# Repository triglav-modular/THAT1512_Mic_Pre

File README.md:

# µAmp
A THAT1512 microphone preamp. This is a very simple board with a THAT1512 based preamp for replacing the one in the Buchla 208 for a much lower noise floor and higher gain. Wire between the preamp jack and T.P.1 on card 10. Lower R6 on card 10 to compensate for the gain increase.

The board is 45 × 24 mm with a single M3 mounting hole. Gain is set by the 1K trimmer (RV1, a Bourns 3362P): about 15 dB at full resistance up to about 59 dB at zero, where the 5.6 Ω R6 sets the top of the range.

## Header pinout

Pin 1 is the square pad.

| Pin | 1 | 2 | 3 | 4 | 5 | 6 | 7 |
|---|---|---|---|---|---|---|---|
| | i+ | i− | g | −v | +v | g | out |

## Revisions

**rev3 (2026)** — same outline, header pinout and mounting hole as rev2, so it is a drop-in replacement.

- Corrected part numbers: U1 is THAT1512P08-U (was 1510), C4/C5 are 100 nF (were 470 pF part numbers), R1/R2 are 1 kΩ (were 6.81 kΩ part numbers), RV1 is 1 kΩ.
- R3 100 Ω in series with the output, to isolate the THAT1512 from the capacitance of the wire to card 10 (it is specified for 300 pF at most).
- R6 5.6 Ω in series with RV1, so maximum gain is set by a resistor rather than by the trimmer's end resistance.
- R4/C7 and R5/C8: 10 Ω and 10 µF on each supply rail.
- No output coupling capacitor is needed: card 10 AC-couples after T.P.1, and C6 holds the output offset to a few mV.

**rev2 (2022)** — the board fitted in the 208, tagged `rev2`. Its raytraced render is `uAmp_3D_render.png`.

## Bill of materials (rev3)

| Ref | Value | Part number | Notes |
|---|---|---|---|
| U1 | THAT1512 | THAT1512P08-U | DIP-8 |
| RV1 | 1 kΩ trimmer | Bourns 3362P-1-102LF | |
| C1, C2 | 470 pF | Murata RDE5C2A471J0M1H03A | C0G, 5 mm pitch |
| C3 | 47 pF | Murata RDE5C2A470J0M1H03A | C0G, 5 mm pitch |
| C4, C5 | 100 nF | Murata RDER71H104K0M1H03A | X7R, 5 mm pitch |
| C6 | 6800 µF 6.3 V | Nichicon UVZ0J682MHD | 12.5 × 25 mm, 5 mm pitch. Polarized is correct here: both gain pins sit at the same DC level. Bipolar 6800 µF only comes as 18 × 35.5 mm, which does not fit |
| C7, C8 | 10 µF 50 V | Panasonic EEU-FR1H100 | 5 mm diameter, 2 mm pitch |
| R1, R2 | 1 kΩ 0.1 % | Vishay CMF551K0000BEEK | |
| R3 | 100 Ω | Vishay MBA02040C1000FC100 | mounted vertically |
| R4, R5 | 10 Ω | Vishay MBA02040C1009FC100 | mounted vertically |
| R6 | 5.6 Ω | Vishay MBB02070C5608FCT00 | mounted vertically |
| J1 | 1×7 pin header | | 2.54 mm |

## Substituting the SSM2019

THAT Corporation put the 1510 and 1512 on end-of-life status on 1 September 2026 ([memo](https://thatcorp.com/wp-content/uploads/2026/09/THAT-EOL-Memo.pdf)). The Analog Devices SSM2019BNZ (DIP-8) has the same pinout and fits U1 with no board change.

Its gain is 1 + 10 kΩ/Rg where the THAT1512's is 0.5 + 5 kΩ/Rg, so with the rev3 values the range moves up about 6 dB, to 21–65 dB. Two value changes bring it back to about 15.5–59 dB:

| Ref | With THAT1512 | With SSM2019 |
|---|---|---|
| R6 | 5.6 Ω | 11 Ω |
| RV1 | 1 kΩ (3362P-1-102LF) | 2 kΩ (3362P-1-202LF) |

Nothing else changes; C6 then rolls off near 2 Hz at full gain instead of 4 Hz.

By the datasheets the SSM2019 matches the THAT1512's 1 nV/√Hz input noise at 60 dB and is a little noisier below 40 dB (7 against 4.6 nV/√Hz at 20 dB). Its bandwidth at 60 dB is 200 kHz against 1.6 MHz, and its distortion there is about twice as high (0.017 % against 0.008 %, measured under different conditions). It drives 5000 pF where the THAT1512 is limited to 300 pF.

The TI INA217 shares the pinout and the SSM2019's gain equation, but TI no longer lists it in DIP-8.

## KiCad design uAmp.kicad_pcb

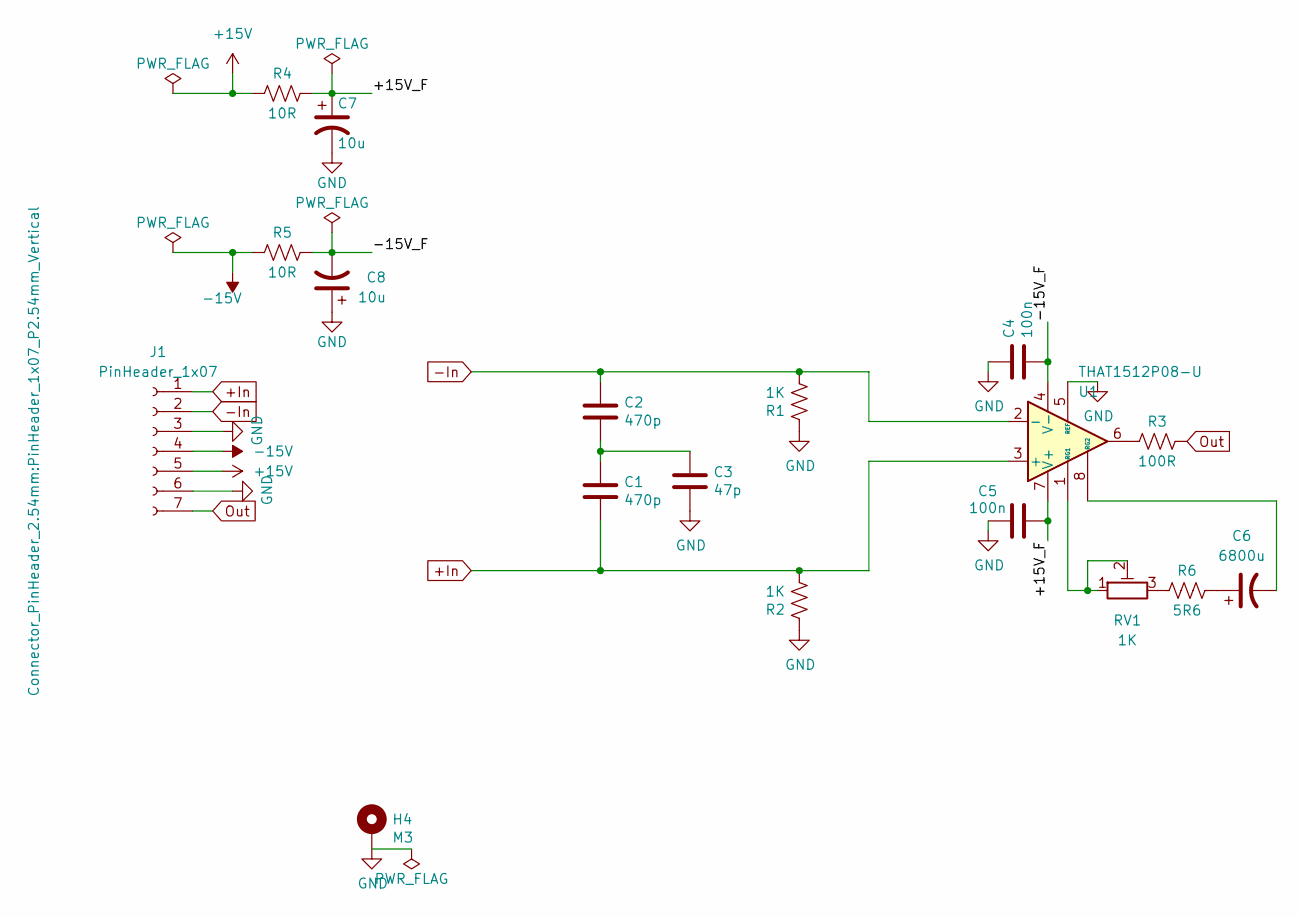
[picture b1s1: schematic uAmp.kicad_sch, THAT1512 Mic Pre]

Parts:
C1, C2: 470p; C_Disc_D5.0mm_W2.5mm_P5.00mm
C3: 47p; C_Disc_D5.0mm_W2.5mm_P5.00mm
C4, C5: 100n; C_Disc_D5.0mm_W2.5mm_P5.00mm
C6: 6800u; CP_Radial_D12.5mm_P5.00mm
C7, C8: 10u; CP_Radial_D5.0mm_P2.00mm
H4: M3; MountingHole_3.2mm_M3_Pad
J1: PinHeader_1x07; PinHeader_1x07_P2.54mm_Vertical
R1, R2: 1K; R_Axial_DIN0207_L6.3mm_D2.5mm_P10.16mm_Horizontal
R3: 100R; R_Axial_DIN0204_L3.6mm_D1.6mm_P2.54mm_Vertical
R4, R5: 10R; R_Axial_DIN0204_L3.6mm_D1.6mm_P2.54mm_Vertical
R6: 5R6; R_Axial_DIN0207_L6.3mm_D2.5mm_P2.54mm_Vertical
RV1: 1K; TRIM_3362P-1-103
U1: THAT1512P08-U; DIP-8_W7.62mm

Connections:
+15V: J1.5, R4.1
+In: C1.2, J1.1, R2.2, U1.3 (+)
-15V: J1.4, R5.1
-In: C2.1, J1.2, R1.2, U1.2 (-)
/+15V_F: C5.2, C7.1, R4.2, U1.7 (V+)
/-15V_F: C4.2, C8.2, R5.2, U1.4 (V-)
GND: C3.2, C4.1, C5.1, C7.2, C8.1, H4.1, J1.3, J1.6, R1.1, R2.1, U1.5 (REF)
unnamed: C1.1, C2.2, C3.1
unnamed: C6.1, R6.2
unnamed: R3.1, U1.6
unnamed: R6.1, RV1.3
unnamed: RV1.1, RV1.2, U1.1 (RG1)
unnamed: C6.2, U1.8 (RG2)
Out: J1.7, R3.2

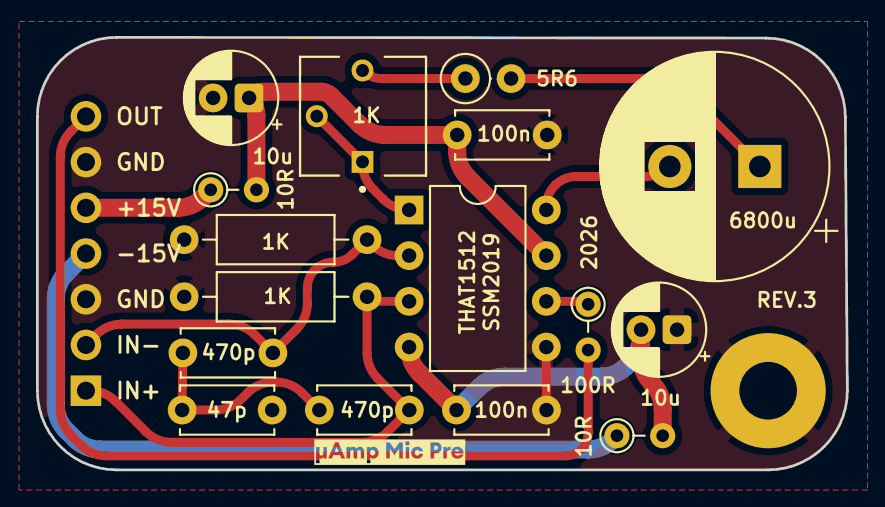
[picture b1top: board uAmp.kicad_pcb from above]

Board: 2 copper layers, 45.0 x 24.0 mm, 18 parts (0 on the bottom side), 14 nets.

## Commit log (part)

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2022-04-22 add 3d render
2022-04-23 change C6 footprint
2022-05-14 rounded
2022-05-15 rounded tracks
